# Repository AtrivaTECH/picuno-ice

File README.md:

# picuno-ice

## CUSTOM PORT OF PICO-ICE to PicUNO compatible FPGA Shield. 

NOTICE: This is an fork of the original project. Multiple changes shall be made for compatibility with PicUNO. Currently being designed. Shield will have similarities to Pico-Ice. 

<br>
<small>PicUNO iCE FPGA shield Render</small>

## PCB Design Files, Designs, Documentation

The pico-ice is a small, low cost board with the Raspberry Pi Pico processor (RP2040) and a Lattice Semiconductor iCE40UP5K FPGA. The board features independent flash for the FPGA and RP2040, low power SSRAM, a couple of pushbuttons and a 3 color LED with _all_ FPGA and RP2040 pins brought out to easy to use 0.1" header pins (arranged as PMOD's) for fast prototyping.

The tinyVision.ai pico-ice Board Features:

* RaspberryPi RP2040 processor
* Lattice UltraPlus ICE40UP5K FPGA with 5.3K LUTs, 1Mb SPRAM, 120Kb DPRAM, 8 Multipliers
* _ALL_ RP2040 and 32 FPGA GPIO on 0.1” headers
* 4MB SPI Flash
* 8MB low power qSPI SRAM
* RGB LED, shared between the RP2040 and FPGA
* 2 pushbuttons, 1 dedicated and 1 primarily for processor reset during development but can be repurposed for user applications when not used for reset
* On board 3.3V and 1.2V Regulators, can supply 3.3V to your project
* Open source schematic and layout using KiCAD design tools
* 4 layer board with a solid ground plane for good signal integrity
* FPGA clock supplied by the RP2040, easy to program FPGA clock under SW control
* Examples for communicating to the FPGA over SPI
* Support for ultra low power sleeep mode: can shut down the RP2040 and FPGA while keeping the SRAM powered

Firmware features:
* pico-ice library to support drag-drop programming of the FPGA bitfile: no need of any dedicated programmer
* Alternate programming of the FPGA flash using DFU mode
* FPGA clock under RP2040 control
* Passthrough UART code enables transparent access to the FPGA's UART for debug/logging/control

### Certifications
PicUNO Shield:

Pico Ice:[OSHW US002140](https://certification.oshwa.org/us002140.html) | Certified open source hardware | oshwa.org/cert

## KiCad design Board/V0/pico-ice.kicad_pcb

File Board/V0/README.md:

Files for the First version of iCE FPGA Shield for PicUNO.

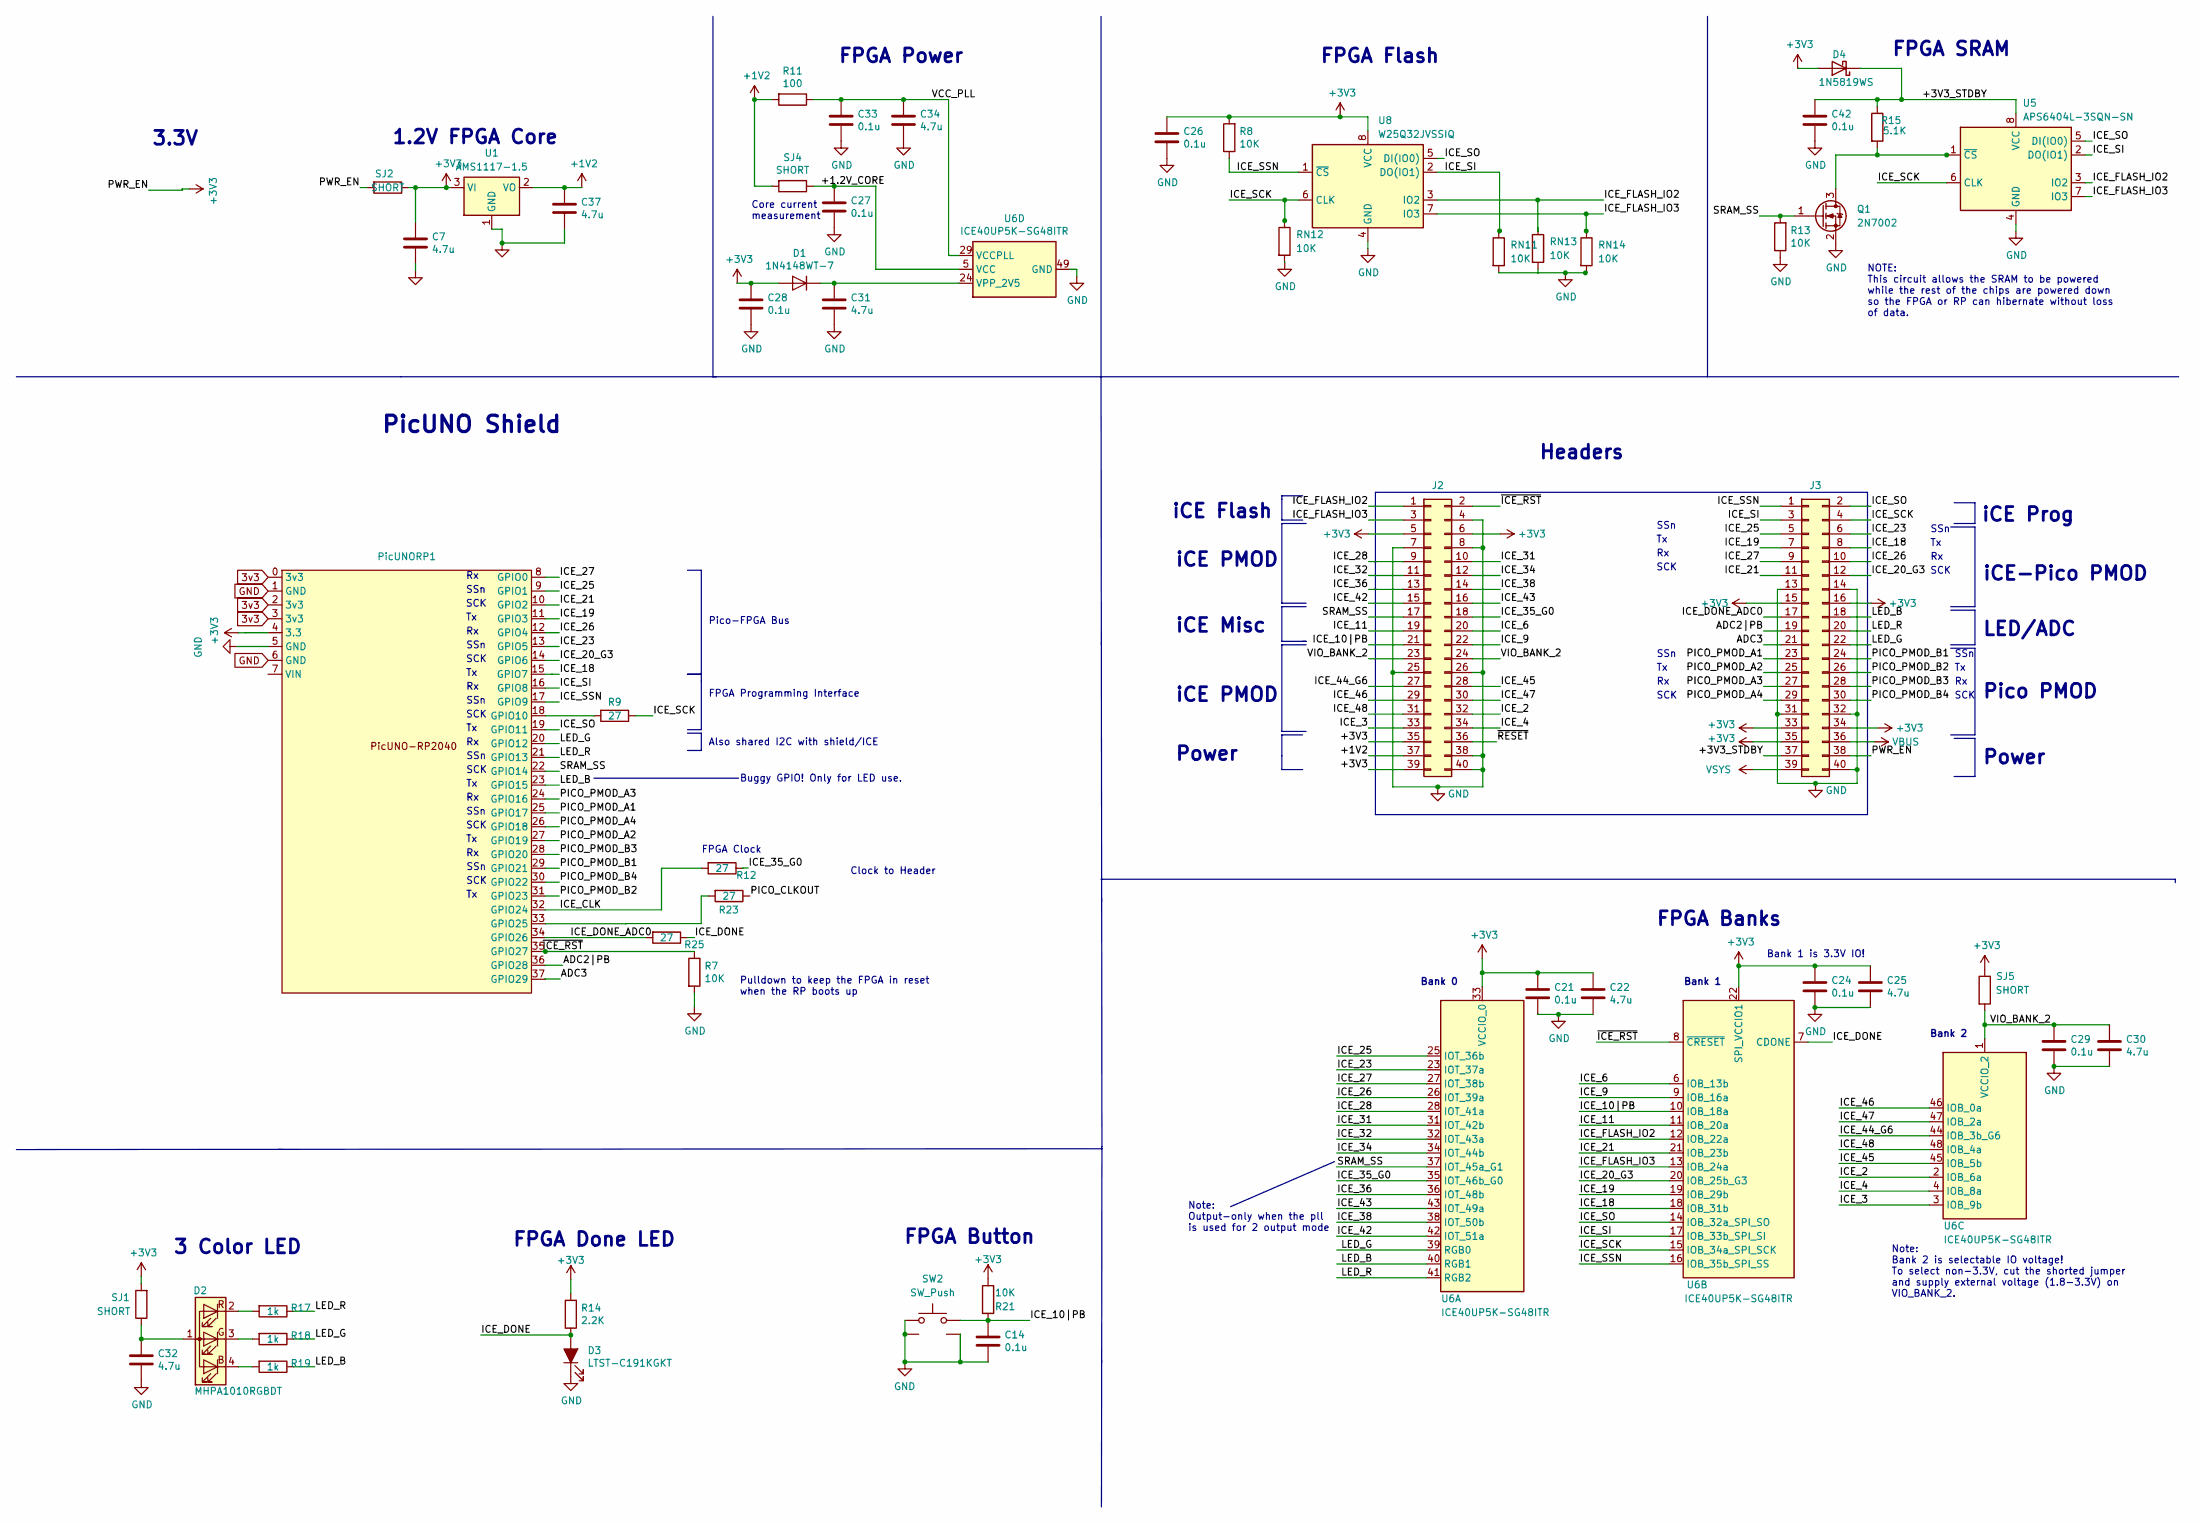
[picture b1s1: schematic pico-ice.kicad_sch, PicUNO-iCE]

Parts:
C7, C25, C30, C34, C37: 4.7u; C_0603_1608Metric; MPN GRM155R60J475ME87D
C14, C24, C26, C27, C28, C29, C33, C42: 0.1u; C_0603_1608Metric; MPN GRM155R71C104KA88J
C21: 0.1u; C_0603_1608Metric_Pad1.08x0.95mm_HandSolder; MPN GRM155R71C104KA88J
C22, C31, C32: 4.7u; C_0603_1608Metric_Pad1.08x0.95mm_HandSolder; MPN GRM155R60J475ME87D
D1: 1N4148WT-7; D_SOD-128; MPN 1N4148WT-7
D2: MHPA1010RGBDT; LED_D5.0mm-4_RGB; MPN MHPA1010RGBDT; Digi-Key Part Number LCSC
D3: LTST-C191KGKT; LED_0805_2012Metric; MPN LTST-C191KGKT
D4: 1N5819WS; D_SOD-128; MPN 1N5819WS
J2: Conn_02x20_Odd_Even; PinHeader_2x20_P2.54mm_Vertical_Left; MPN DNP
J3: Conn_02x20_Odd_Even; PinHeader_2x20_P2.54mm_Vertical_Right; MPN DNP
PicUNORP1: PicuNO RP2040
Q1: 2N7002; SOT-23; MPN 2N7002
R7: 10K; R_0402_1005Metric; MPN DNP
R8, R13: 10K; R_0603_1608Metric_Pad0.98x0.95mm_HandSolder; MPN RC0402FR-0710KL
R9, R12, R23, R25: 27; R_0402_1005Metric; MPN RC0402FR-0727RL
R11: 100; R_0603_1608Metric; MPN RC0402FR-07100RL
R14: 2.2K; R_0603_1608Metric; MPN RC0402FR-072K2L
R15: 5.1K; R_0603_1608Metric; MPN RC0402FR-075K1L
R17, R19: 1k; R_0603_1608Metric_Pad0.98x0.95mm_HandSolder; MPN RC0402FR-071KL
R18: 1k; R_0603_1608Metric; MPN RC0402FR-071KL
R21: 10K; R_0603_1608Metric; MPN RC0402FR-0710KL
RN11, RN12, RN13, RN14: 10K; R_0603_1608Metric_Pad0.98x0.95mm_HandSolder
SJ1, SJ2, SJ4, SJ5: SHORT; SolderJumper-2_P1.3mm_Bridged_RoundedPad1.0x1.5mm; MPN DNP
SW2: PTS820 J25K SMTR LFS; SW_SPST_TL3342; MPN PTS820 J25K SMTR LFS
U1: AMS1117-1.5; SOT-223-3_TabPin2
U5: APS6404L-3SQN-SN; SOIC-8_3.9x4.9mm_P1.27mm; MPN APS6404L-3SQN-SN
U6: ICE40UP5K-SG48ITR; QFN-48-1EP_7x7mm_P0.5mm_EP5.6x5.6mm; MPN ICE40UP5K-SG48I
U8: W25Q32JVSSIQ; SOIC-8_5.23x5.23mm_P1.27mm; MPN W25Q32JVSSIQ

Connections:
3v3: PicUNORP1.0 (3v3), PicUNORP1.2 (3v3), PicUNORP1.3 (3v3)
+1V2: C37.1, J2.37, R11.2, SJ4.2, U1.2 (VO)
+3V3: C7.1, C21.1, C22.1, C24.1, C25.1, C26.1, C28.1, D1.2 (A), D4.2 (A), J2.5, J2.6, J2.35, J2.39, J3.15, J3.16, J3.33, J3.34, J3.35, J3.38, PicUNORP1.4 (3.3), R8.2, R14.2, R21.1, SJ1.2, SJ2.1, SJ2.2, SJ5.1, U1.3 (VI), U6.22 (SPI_VCCIO1), U6.33 (VCCIO_0), U8.8 (VCC)
/+1.2V_CORE: C27.1, SJ4.1, U6.5 (VCC), U6.30 (VCC)
/+3V3_STDBY: C42.1, D4.1 (K), J3.37, R15.1, U5.8 (VCC)
/ADC2|PB: J3.19, PicUNORP1.36 (GPIO28)
/ADC3: J3.21, PicUNORP1.37 (GPIO29)
/ICE_2: J2.32, U6.2 (IOB_6a)
/ICE_3: J2.33, U6.3 (IOB_9b)
/ICE_4: J2.34, U6.4 (IOB_8a)
/ICE_6: J2.20, U6.6 (IOB_13b)
/ICE_9: J2.22, U6.9 (IOB_16a)
/ICE_10|PB: C14.1, J2.21, R21.2, SW2.2, U6.10 (IOB_18a)
/ICE_11: J2.19, U6.11 (IOB_20a)
/ICE_18: J3.8, PicUNORP1.15 (GPIO7), U6.18 (IOB_31b)
/ICE_19: J3.7, PicUNORP1.11 (GPIO3), U6.19 (IOB_29b)
/ICE_20_G3: J3.12, PicUNORP1.14 (GPIO6), U6.20 (IOB_25b_G3)
/ICE_21: J3.11, PicUNORP1.10 (GPIO2), U6.21 (IOB_23b)
/ICE_23: J3.6, PicUNORP1.13 (GPIO5), U6.23 (IOT_37a)
/ICE_25: J3.5, PicUNORP1.9 (GPIO1), U6.25 (IOT_36b)
/ICE_26: J3.10, PicUNORP1.12 (GPIO4), U6.26 (IOT_39a)
/ICE_27: J3.9, PicUNORP1.8 (GPIO0), U6.27 (IOT_38b)
/ICE_28: J2.9, U6.28 (IOT_41a)
/ICE_31: J2.10, U6.31 (IOT_42b)
/ICE_32: J2.11, U6.32 (IOT_43a)
/ICE_34: J2.12, U6.34 (IOT_44b)
/ICE_35_G0: J2.18, R12.1, U6.35 (IOT_46b_G0)
/ICE_36: J2.13, U6.36 (IOT_48b)
/ICE_38: J2.14, U6.38 (IOT_50b)
/ICE_42: J2.15, U6.42 (IOT_51a)
/ICE_43: J2.16, U6.43 (IOT_49a)
/ICE_44_G6: J2.27, U6.44 (IOB_3b_G6)
/ICE_45: J2.28, U6.45 (IOB_5b)
/ICE_46: J2.29, U6.46 (IOB_0a)
/ICE_47: J2.30, U6.47 (IOB_2a)
/ICE_48: J2.31, U6.48 (IOB_4a)
/ICE_CLK: PicUNORP1.32 (GPIO24), R12.2
/ICE_DONE: D3.2 (A), R14.1, R25.1, U6.7 (CDONE)
/ICE_DONE_ADC0: J3.17, PicUNORP1.34 (GPIO26), R25.2
/ICE_FLASH_IO2: J2.1, RN13.1, U5.3 (IO2), U6.12 (IOB_22a), U8.3 (IO2)
/ICE_FLASH_IO3: J2.3, RN14.1, U5.7 (IO3), U6.13 (IOB_24a), U8.7 (IO3)
/ICE_SCK: J3.4, R9.1, RN12.1, U5.6 (CLK), U6.15 (IOB_34a_SPI_SCK), U8.6 (CLK)
/ICE_SI: J3.3, PicUNORP1.16 (GPIO8), RN11.1, U5.2 (DO(IO1)), U6.17 (IOB_33b_SPI_SI), U8.2 (DO(IO1))
/ICE_SO: J3.2, PicUNORP1.19 (GPIO11), U5.5 (DI(IO0)), U6.14 (IOB_32a_SPI_SO), U8.5 (DI(IO0))
/ICE_SSN: J3.1, PicUNORP1.17 (GPIO9), R8.1, U6.16 (IOB_35b_SPI_SS), U8.1 (~CS)
/LED_B: J3.18, PicUNORP1.23 (GPIO15), R19.1, U6.40 (RGB1)
/LED_G: J3.22, PicUNORP1.20 (GPIO12), R18.1, U6.39 (RGB0)
/LED_R: J3.20, PicUNORP1.21 (GPIO13), R17.1, U6.41 (RGB2)
/PICO_CLKOUT: R23.1
/PICO_PMOD_A1: J3.23, PicUNORP1.25 (GPIO17)
/PICO_PMOD_A2: J3.25, PicUNORP1.27 (GPIO19)
/PICO_PMOD_A3: J3.27, PicUNORP1.24 (GPIO16)
/PICO_PMOD_A4: J3.29, PicUNORP1.26 (GPIO18)
/PICO_PMOD_B1: J3.24, PicUNORP1.29 (GPIO21)
/PICO_PMOD_B2: J3.26, PicUNORP1.31 (GPIO23)
/PICO_PMOD_B3: J3.28, PicUNORP1.28 (GPIO20)
/PICO_PMOD_B4: J3.30, PicUNORP1.30 (GPIO22)
/SRAM_SS: J2.17, PicUNORP1.22 (GPIO14), Q1.1 (G), R13.2, U6.37 (IOT_45a_G1)
/VCC_PLL: C33.1, C34.1, R11.1, U6.29 (VCCPLL)
/VIO_BANK_2: C29.1, C30.1, J2.23, J2.24, SJ5.2, U6.1 (VCCIO_2)
/~ICE_RST: J2.2, PicUNORP1.35 (GPIO27), R7.1, U6.8 (~CRESET)
/~RESET: J2.36
GND: C7.2, C14.2, C21.2, C22.2, C24.2, C25.2, C26.2, C27.2, C28.2, C29.2, C30.2, C31.2, C32.2, C33.2, C34.2, C37.2, C42.2, D3.1 (K), J2.4, J2.7, J2.8, J2.25, J2.26, J2.38, J2.40, J3.13, J3.14, J3.31, J3.32, J3.40, PicUNORP1.1 (GND), PicUNORP1.5 (GND), PicUNORP1.6 (GND), Q1.2 (S), R7.2, R13.1, RN11.2, RN12.2, RN14.2, SW2.1, SW2.SH1, SW2.SH2, U1.1 (GND), U5.4 (GND), U6.49 (GND), U8.4 (GND)
unnamed: C31.1, D1.1 (K), U6.24 (VPP_2V5)
unnamed: C32.1, D2.1 (A), SJ1.1
unnamed: D2.4 (BK), R19.2
unnamed: D2.3 (GK), R18.2
unnamed: D2.2 (RK), R17.2
unnamed: PicUNORP1.18 (GPIO10), R9.2
unnamed: PicUNORP1.33 (GPIO25), R23.2
unnamed: Q1.3 (D), R15.2, U5.1 (~CS)
VBUS: J3.39
VDC: J3.36

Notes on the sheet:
FPGA SRAM
iCE PMOD
FPGA Programming Interface
SCK
1.2V FPGA Core
Pico PMOD
NOTE: This circuit allows the SRAM to be powered while the rest of the chips are powered down so the FPGA or RP can hibernate without loss of data.
SSn
Note: Output-only when the pll is used for 2 output mode
FPGA Clock
Bank 1 is 3.3V IO!
FPGA Power
Bank 2
Pico-FPGA Bus
iCE Misc
FPGA Button
Pulldown to keep the FPGA in reset when the RP boots up
Headers
LED/ADC
3 Color LED
Clock to Header
Power
Note: Bank 2 is selectable IO voltage! To select non-3.3V, cut the shorted jumper and supply external voltage (1.8-3.3V) on VIO_BANK_2.
FPGA Banks
Buggy GPIO! Only for LED use.
Also shared I2C with shield/ICE
iCE-Pico PMOD
Bank 0
PicUNO Shield
iCE Flash
Core current measurement
FPGA Done LED
Bank 1
FPGA Flash
3.3V
iCE Prog

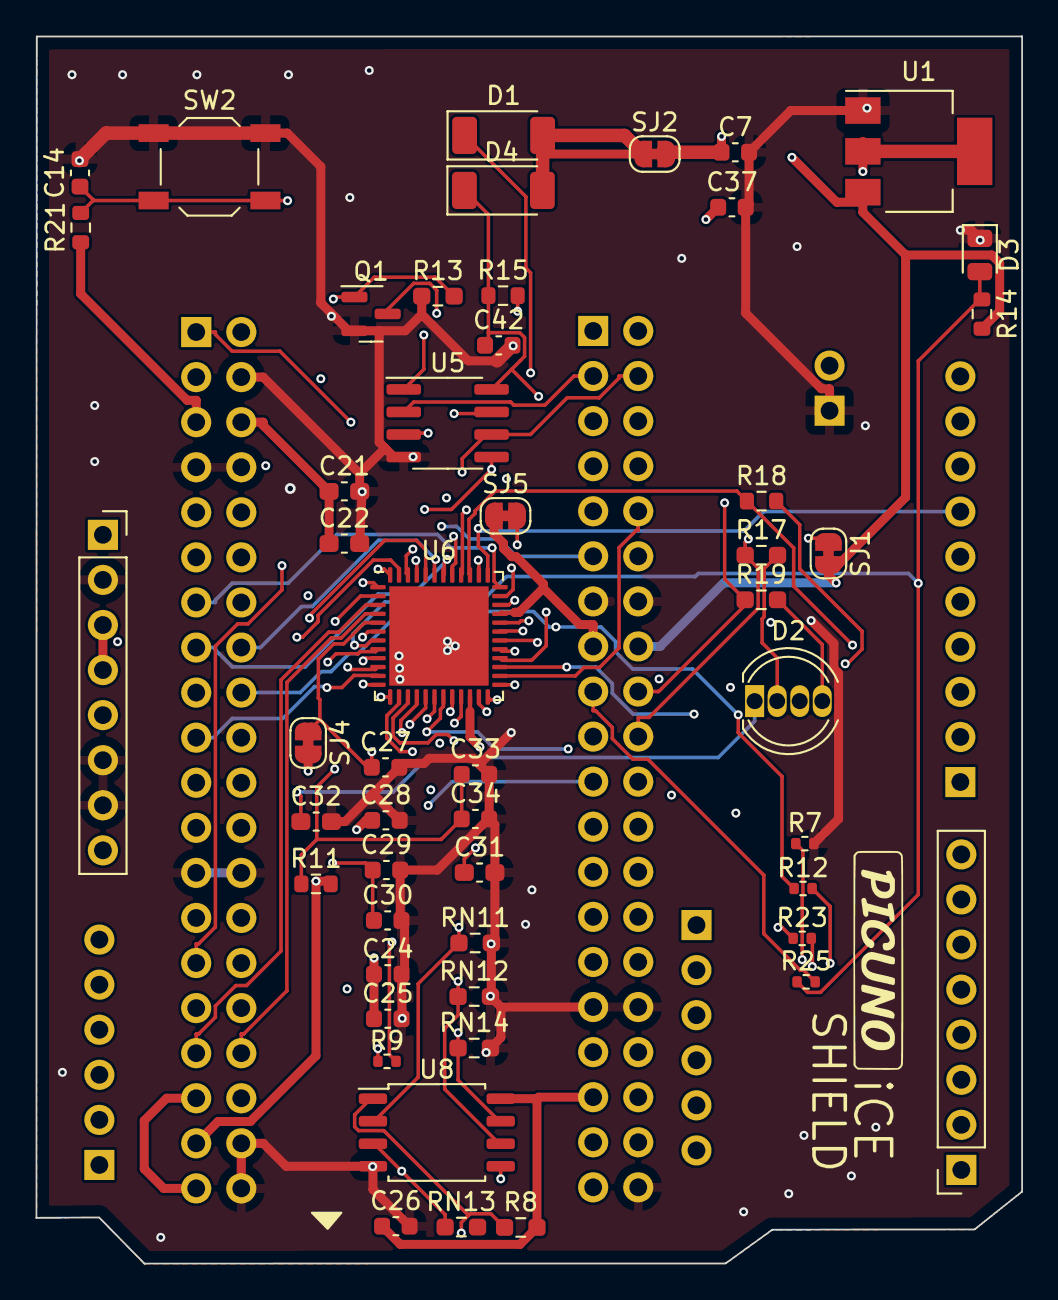
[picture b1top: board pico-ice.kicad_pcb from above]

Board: 4 copper layers, 55.5 x 69.2 mm, 52 parts (0 on the bottom side), 69 nets.

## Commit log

2024-04-17 Update LICENSE
2024-04-17 V0 Kicad Files added via Upload
